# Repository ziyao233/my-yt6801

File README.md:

# YT6801-based GbE NIC

A GbE NIC based on Motorcomm YT6801.

## Components

- Motorcomm YT6801 (QFN-32), the NIC chip.
- Hanrun HR911130A, RJ45 connector with integrated ethernet transformer.

The entire BoM costs less than 20CNY on Taobao at the time of writing.

## Driver

AOSC OS and Deepin Linux have the driver for Motorcomm YT6801 built in their
kernels.

An out-of-tree module maintained by myself could be found [here](https://github.com/ziyao233/yt6801-vendor-driver).
If possible, please also consider the in-progress [patches to upstream Linux kernel](https://lore.kernel.org/netdev/20251225071914.1903-1-me@ziyao.cc/)
which is considered more robust.

## License

The project is distributed under CC-BY-SA-4.0.

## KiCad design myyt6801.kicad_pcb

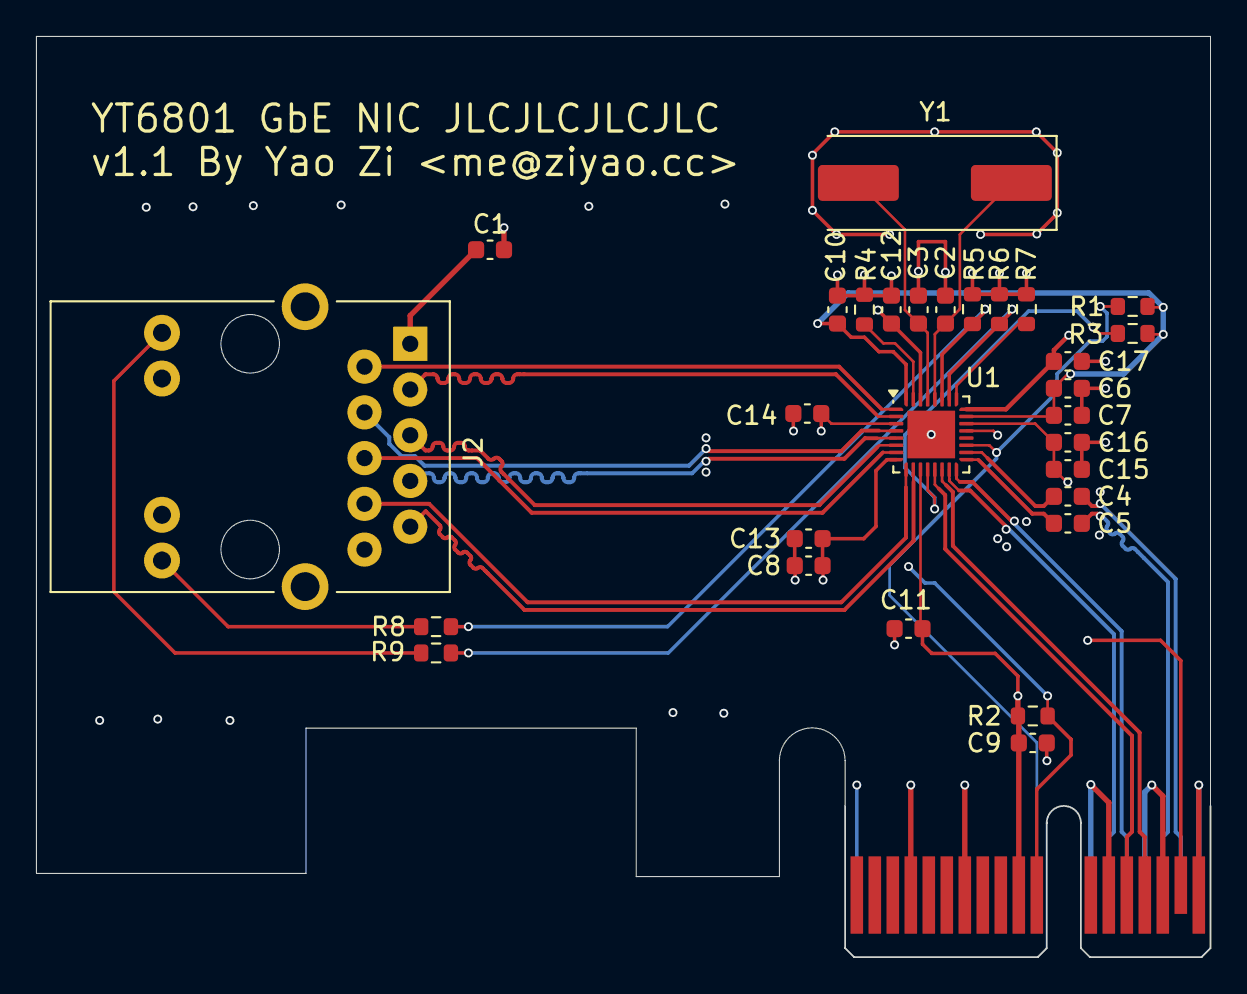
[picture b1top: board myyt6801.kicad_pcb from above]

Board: 4 copper layers, 65.2 x 51.1 mm, 30 parts (0 on the bottom side), 32 nets.

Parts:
C1, C4, C5, C7, C10, C11, C12, C13, C14, C16, C17: 100nF; C_0603_1608Metric
C2, C3: 32pF; C_0603_1608Metric
C6, C9: 4.7uF; C_0603_1608Metric
C8, C15: 1uF; C_0603_1608Metric
J1: Bus_PCI_Express_x1; BUS_PCIexpress_x1
J2: HR911130A; RJ45_HR911130A
R1, R3: 10K; R_0603_1608Metric
R2: 1K; R_0603_1608Metric
R4: 2.49K 1%; R_0603_1608Metric
R5, R6, R7: 4.7K; R_0603_1608Metric
R8, R9: 330; R_0603_1608Metric
U1: YT6801; QFN-32-1EP_4x4mm_P0.4mm_EP2.65x2.65mm
Y1: HC-49SMD 25MHz; Crystal_SMD_HC49-SD

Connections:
+1V2: C8.1, C12.1, C13.1, C14.1, C15.1, C16.1, C17.1, U1.3 (AVDD12), U1.8 (AVDD12), U1.22 (DVDD12), U1.24 (REGOUT), U1.30 (AVDD12)
+3V3: C6.1, C7.1, C9.1, C10.1, C11.1, J1.B10 (3.3Vaux), R1.2, R2.2, R3.2, U1.11 (AVDD33), U1.23 (VDDREG), U1.32 (AVDD33)
/CLKREQ#: R3.1, U1.12 (#CLKREQ)
/HSI_N: J1.B15 (PETn0), U1.14 (HSI_N)
/HSI_P: J1.B14 (PETp0), U1.13 (HSI_P)
/HSO_N: C4.1, U1.18 (HSO_N)
/HSO_P: C5.2, U1.17 (HSO_P)
/LED0: R5.1, R8.1, U1.27 (LED0)
/LED1: R6.2, R9.1, U1.26 (LED1)
/LED2: R7.1, U1.25 (LED2)
/PERST#: J1.A11 (~PERST), R1.1, U1.19 (PERST#)
/PER_N: C4.2, J1.A17 (PERn0)
/PER_P: C5.1, J1.A16 (PERp0)
/REFCLK_N: J1.A14 (REFCLK-), U1.16 (REFCLK_N)
/REFCLK_P: J1.A13 (REFCLK+), U1.15 (REFCLK_P)
/TRX0_N: J2.R3 (TD1-), U1.2 (TRX0_N)
/TRX0_P: J2.R2 (TD1+), U1.1 (TRX0_P)
/TRX1_N: J2.R7 (TD2-), U1.5 (TRX1_N)
/TRX1_P: J2.R4 (TD2+), U1.4 (TRX1_P)
/TRX2_N: J2.R6 (TD3-), U1.7 (TRX2_N)
/TRX2_P: J2.R5 (TD3+), U1.6 (TRX2_P)
/TRX3_N: J2.R9 (TD4-), U1.10 (TRX3_N)
/TRX3_P: J2.R8 (TD4+), U1.9 (TRX3_P)
/WAKE#: J1.B11 (~WAKE), R2.1, U1.21 (WAKE#)
/XTAL_I: C2.1, U1.28 (XTAL_I), Y1.1
/XTAL_O: C3.1, U1.29 (XTAL_O), Y1.2
GND: C1.2, C2.2, C3.2, C6.2, C7.2, C8.2, C9.2, C10.2, C11.2, C12.2, C13.2, C14.2, C15.2, C16.2, C17.2, J1.A4 (GND), J1.A12 (GND), J1.A15 (GND), J1.A18 (GND), J1.B4 (GND), J1.B7 (GND), J1.B13 (GND), J1.B16 (GND), J1.B18 (GND), J2.L2, J2.L4, J2.R10 (GND), J2.SH, R4.1, R5.2, R6.1, R7.2, U1.33 (GND)
unnamed: J1.A1 (~PRSNT1), J1.B17 (~PRSNT2)
unnamed: C1.1, J2.R1 (CT)
unnamed: J2.L1, R9.2
unnamed: J2.L3, R8.2
unnamed: R4.2, U1.31 (RBIAS)

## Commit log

2026-01-06 v1.1 design
2026-01-06 Add assets
2026-01-06 Add a README
